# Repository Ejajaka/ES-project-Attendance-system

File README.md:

# Shusseki - continuous room attendance with BLE, WiFi and ultrasound

Shusseki is a room-level continuous attendance system. A fixed ESP32 node
advertises a BLE rolling code, hosts the room WiFi network and emits an
ultrasonic presence stamp. Phones in the room report BLE, WiFi and ultrasonic
measurements to a fusion server, which maintains a live roster and a human
register. An RFID reader on the node also marks students who tap a card.

The project compares BLE-only, WiFi-only, ultrasonic-only and fused presence
against a manually counted ground truth.

## Components

```
/shared/            Pure TypeScript logic: rolling codes, confidence, fusion,
                    evaluation metrics and report schemas. Vitest-tested.
/server/            Hono fusion server: ingest reports, verify codes, presence,
                    roster, attendance register, live dashboard and CSV export.
/app/               Expo / React Native app:
                      Soshin (transmitter) - phone-side beacon fallback
                      Jushin (receiver)    - BLE/WiFi/ultrasound reporting
                    Native modules for BLE, WiFi, ultrasonic and biometric.
/esp32-transmitter/ ESP-IDF firmware for the room node:
                      BLE beacon + open `atlas` SoftAP + NAPT
                      MFRC522 RFID reader + I2C LCD + active/passive buzzers
                      20 kHz ultrasonic transmitter on GPIO27
/evaluation/        Comparative-study runner (BLE / WiFi / ultrasonic / fused).
/docs/              Wiring, attendance flow, test protocol, runbooks and ADRs.
```

The current node build does **not** use a microSD card or push buttons. Card
bindings live in NVS and taps are posted directly to the server.

## Quick start

Prerequisites: Node >= 20 and npm. For the app, use the Expo toolchain and an
Android device/emulator with the Android SDK.

```bash
# install workspace dependencies
npm install

# run the full Vitest suite
npm test

# start the fusion server on http://localhost:8787
npm run dev:server

# run the comparative evaluation sample
cd evaluation && npm run run:sample
```

### Server API

- `POST /api/sessions` - create a session (shares the rolling-code secret).
- `POST /api/reports` - ingest a `DeviceReport`.
- `POST /api/sessions/:id/telemetry` - 0.5 s graph sample.
- `GET  /api/sessions/:id/series` - live BLE/WiFi/SNR series.
- `GET  /dashboard/:id` - live browser charts.
- `GET  /api/sessions/:id/presence` - latest per-device presence.
- `POST /api/sessions/:id/hotspot` - publish the room hotspot.
- `GET  /api/sessions/:id/hotspot` - read the room hotspot.
- `POST /api/sessions/:id/ground-truth` - record a manual headcount.
- `GET  /api/sessions/:id/evaluate` - count error and per-modality metrics.
- `GET  /api/sessions/:id/register` - live attendance register.
- `POST /api/sessions/:id/rfid` - card tap (UID -> student).
- `POST /api/sessions/:id/rfid/bind` - bind a phone-entered UID to a student.

### App

```bash
cd app
npx expo start
```

Pick **TRANSMITTER** (phone-side fallback) or **RECEIVER** (joins the ESP32's
open `atlas` network and reports BLE/WiFi/ultrasound). Set
`EXPO_PUBLIC_SERVER_URL` to the server address (default
`http://10.0.2.2:8787` for the Android emulator). The receiver console shows
raw sensor values, per-modality and fused confidence, the server verdict and a
live BLE/WiFi trace.

The receiver's identity is locked after enrollment. To change the student or
RFID UID, clear the app data, or edit the roster from the server register page.

## ESP32 room node

Wiring, pin map and RFID card details: [`docs/hardware-wiring.md`](docs/hardware-wiring.md).

```bash
cd esp32-transmitter
pio run                 # build
pio run -t upload       # flash (115200 baud)
pio device monitor      # serial log
```

The node:

- advertises `esp32-tx1|<TOTP code>` over BLE;
- raises the open `atlas` SoftAP and routes clients to the LAN via NAPT;
- emits four alternating 20/19.6 kHz bursts on GPIO27;
- polls the server for the live attendance count and shows it on the LCD;
- reads MFRC522 cards and posts the UID to the attendance register;
- shows a student's name (scrolling if long) and roll number on a tap;
- beeps once for a known card, twice for an unknown/new card or saved mapping.

## Tests and deployment

```bash
npm test
npm run typecheck
```

Every APK carries a build number from `app/src/version.ts` (`BUILD`), shown on
the home screen and logged at startup as `[app] version vX.Y.Z+BUILD`. Build a
self-contained release APK with the Expo/Android toolchain and install it with
`adb install -r app/build/outputs/apk/release/app-release.apk`.

For USB-connected devices the server is reachable with
`adb reverse tcp:8787 tcp:8787`.

## Current limitations

- A single ultrasonic beacon is not a strict room boundary: 20 kHz leaks
  through open doors and walls, so "tone heard" only means the tone is present.
  The BLE/WiFi gate is the actual room-presence decision.
- The node has no offline queue. A card tap made while the server is unreachable
  still resolves from NVS and displays on the LCD, but is not replayed later.
- The phone receiver must be on the room network to reach the server; the
  `atlas` SoftAP + NAPT path is the fallback.

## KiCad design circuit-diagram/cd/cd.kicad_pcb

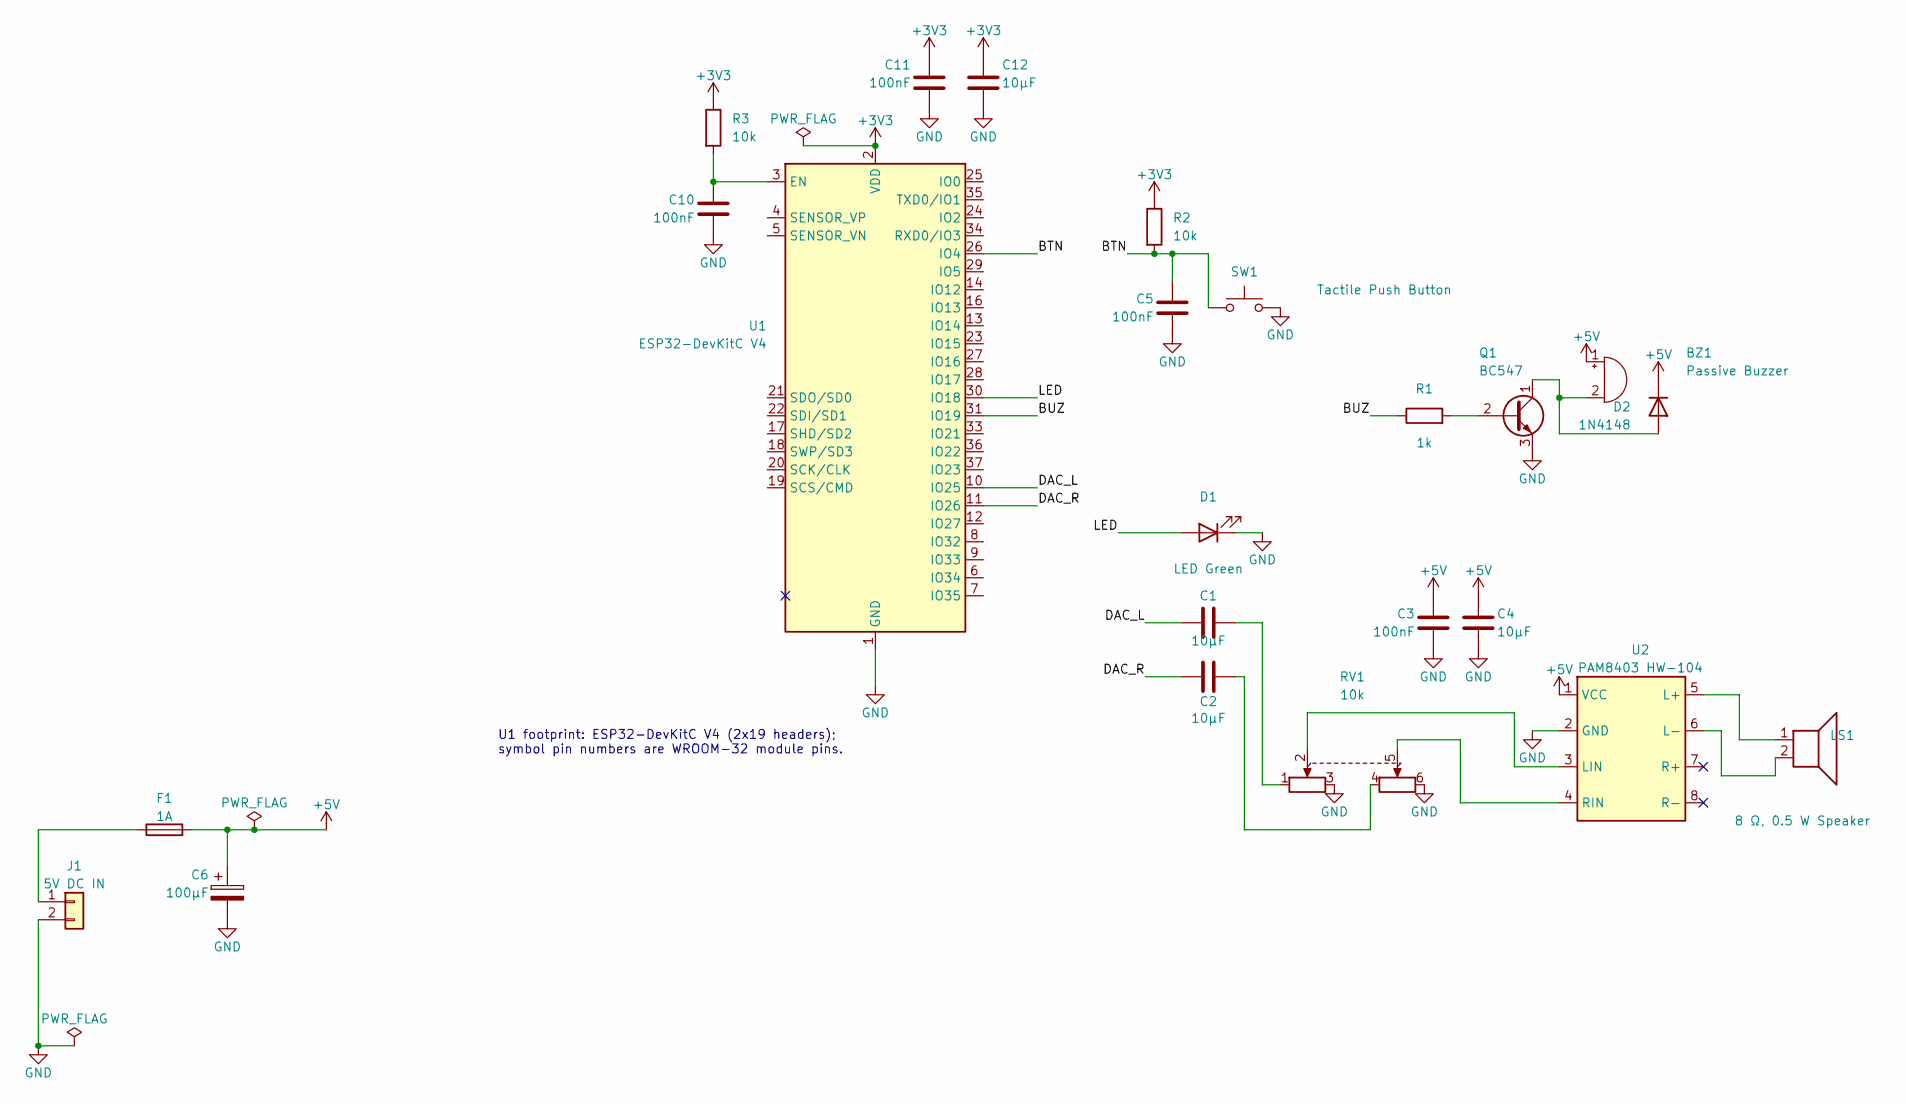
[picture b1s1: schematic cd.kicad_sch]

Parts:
BZ1: Passive Buzzer; PinHeader_1x02_P2.54mm_Vertical
C1, C2, C4, C12: 10µF; C_Disc_D5.0mm_W2.5mm_P5.00mm
C3, C5, C10, C11: 100nF; C_Disc_D5.0mm_W2.5mm_P5.00mm
C6: 100µF; CP_Radial_D6.3mm_P2.50mm
D1: LED Green; LED_D5.0mm
D2: 1N4148; D_DO-35_SOD27_P7.62mm_Horizontal
F1: 1A; Fuse_Bourns_MF-RG300
J1: 5V DC IN; TerminalBlock_Phoenix_MKDS-1,5-2_1x02_P5.00mm_Horizontal
LS1: 8 Ω, 0.5 W Speaker; PinHeader_1x02_P2.54mm_Vertical
Q1: BC547; TO-92_Inline_Wide
R1: 1k; R_Axial_DIN0207_L6.3mm_D2.5mm_P7.62mm_Horizontal
R2, R3: 10k; R_Axial_DIN0207_L6.3mm_D2.5mm_P7.62mm_Horizontal
RV1: 10k; PinHeader_2x03_P2.54mm_Vertical
SW1: Tactile Push Button; SW_PUSH_6mm
U1: ESP32-DevKitC V4; ESP32-DevKitC-V4
U2: PAM8403 HW-104; PAM8403-HW104

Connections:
+3V3: C11.1, C12.1, R2.1, R3.1, U1.2 (VDD)
+5V: BZ1.1 (+), C3.1, C4.1, C6.1, D2.1 (K), F1.2, U1.5V, U2.1 (VCC)
/BTN: C5.1, R2.2, SW1.1, U1.26 (IO4)
/BUZ: R1.1, U1.31 (IO19)
/DAC_L: C1.1, U1.10 (IO25)
/DAC_R: C2.1, U1.11 (IO26)
/LED: D1.2 (A), U1.30 (IO18)
GND: C3.2, C4.2, C5.2, C6.2, C10.2, C11.2, C12.2, D1.1 (K), J1.2, Q1.3 (E), RV1.3, RV1.6, SW1.2, U1.1 (GND), U1.15 (GND), U1.38 (GND), U1.39 (GND), U2.2 (GND)
unnamed: BZ1.2 (-), D2.2 (A), Q1.1 (C)
unnamed: C1.2, RV1.1
unnamed: C2.2, RV1.4
unnamed: F1.1, J1.1
unnamed: Q1.2 (B), R1.2
unnamed: C10.1, R3.2, U1.3 (EN)
unnamed: LS1.1, U2.5 (L+)
unnamed: LS1.2, U2.6 (L-)
unnamed: RV1.2, U2.3 (LIN)
unnamed: RV1.5, U2.4 (RIN)

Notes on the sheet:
U1 footprint: ESP32-DevKitC V4 (2x19 headers); symbol pin numbers are WROOM-32 module pins.

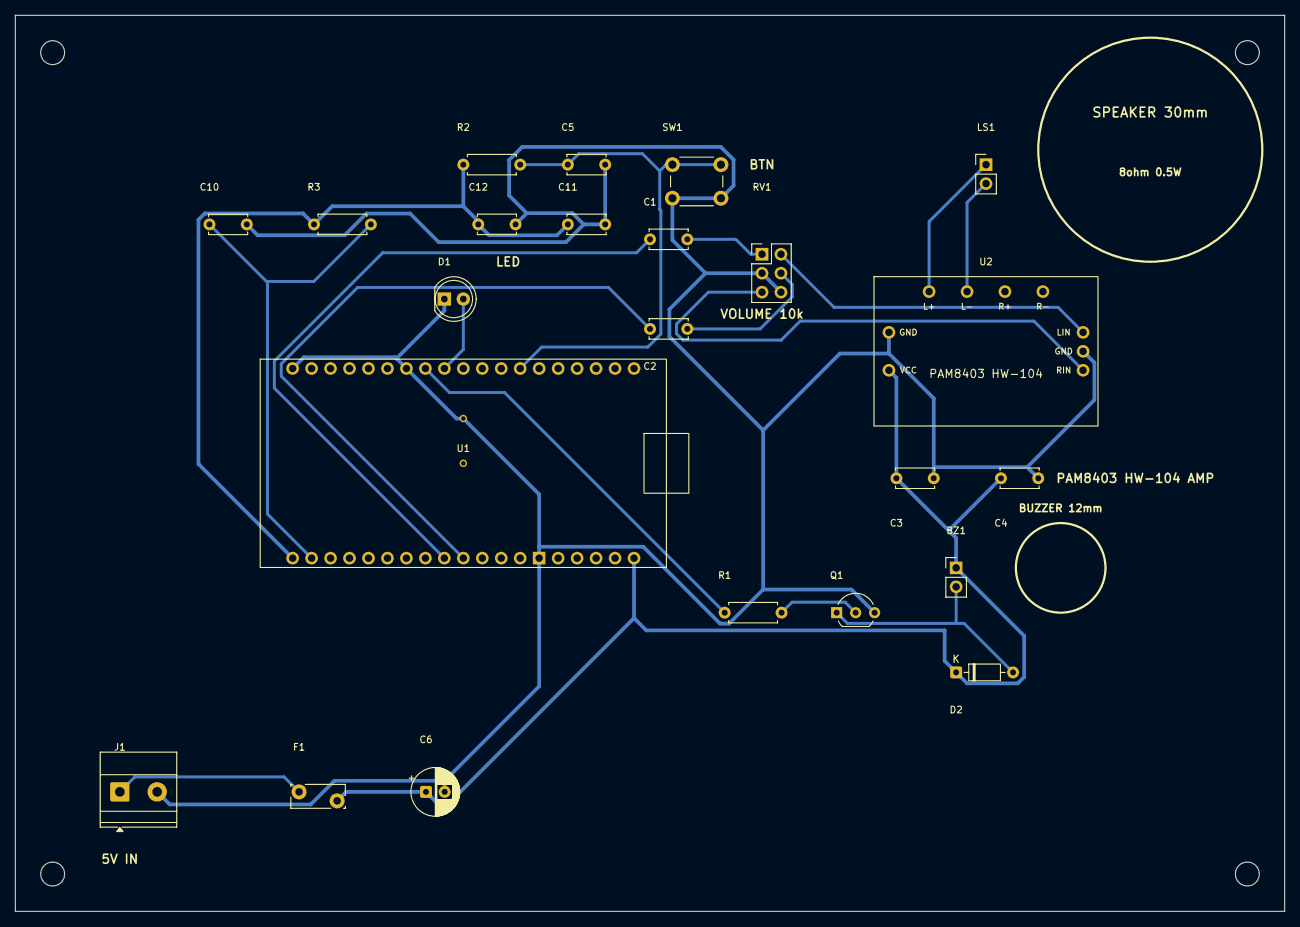
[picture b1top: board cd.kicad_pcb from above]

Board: 2 copper layers, 170.0 x 120.0 mm, 27 parts (0 on the bottom side), 18 nets.

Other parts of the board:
H1, H2, H3, H4: MountingHole_3.2mm_M3
